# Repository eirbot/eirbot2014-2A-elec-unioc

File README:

Avant commencer, je ecris cette README pour aider les personnes que veulent participer du projet electronique pour 2014 (et pour souvenir que je [Felipe] suis bresilien, donc il aura des erreurs de français [ne hesite pas en corrigir])
Pour utilizer correctement ce repositoire, les pas suivants doivent etre suivis:
-2. Inscrivez-vous sur https://github.com/ (c'est facile, il demande seulement un nom d'utilisateur, mot de passe et e-mail)
-1. Comuniquez au responsable (Loic, je pense) pour vous inscriver sur elec_2014
0. Lisez cette README.
1. Telechargez le derniere version de KiCAD
2. Telechargez le GitHub (le method le plus facile est cliquer sur le bouton "Clone in Desktop")
3. Avec GitHub instalé, faisez le login sur le logiciel et demandez pour que le repositoire être syncronisé.
4. Les archives vont être dans <~/Mes Documents/GitHub>. Vous pouvez leur changer, mais aprés vous devez faire la syncronisation avec GitHub

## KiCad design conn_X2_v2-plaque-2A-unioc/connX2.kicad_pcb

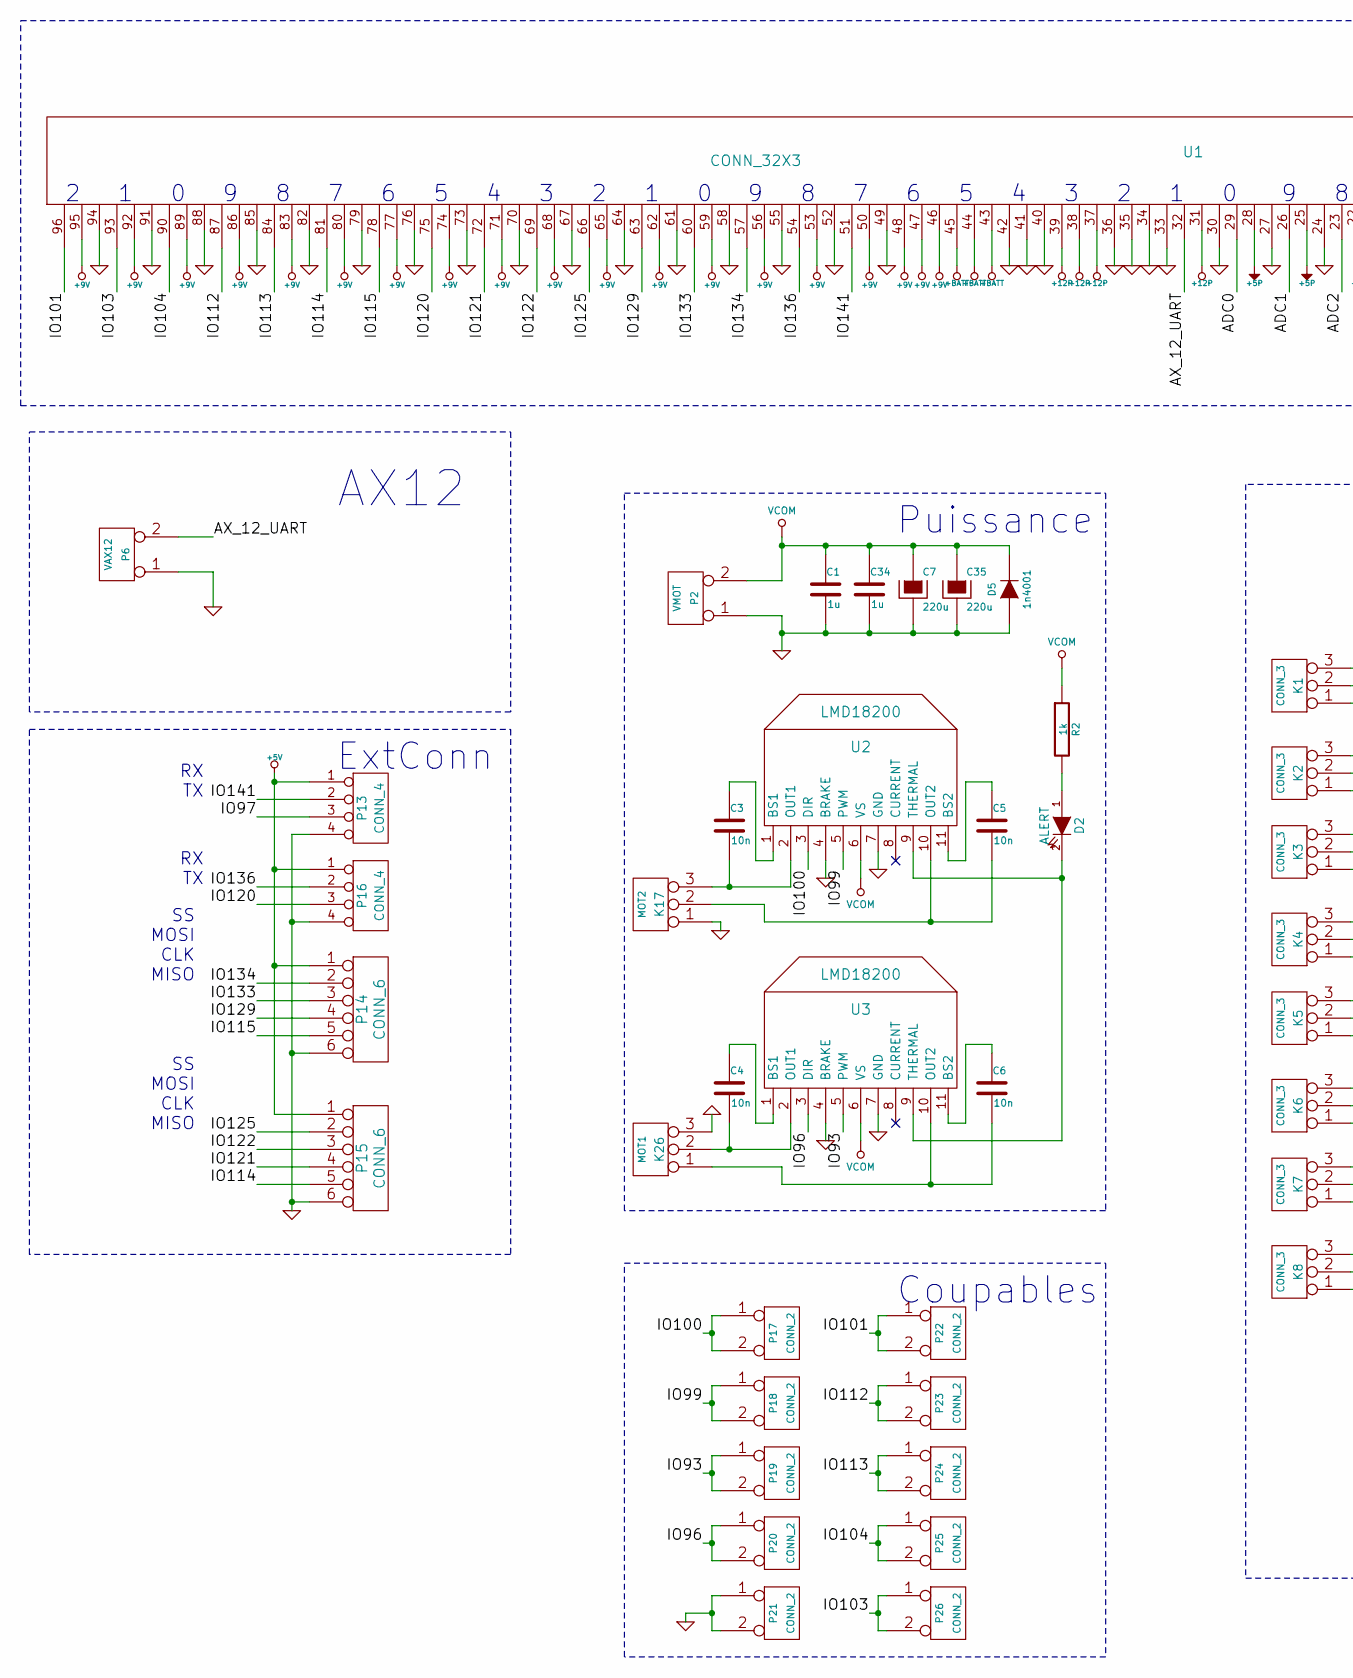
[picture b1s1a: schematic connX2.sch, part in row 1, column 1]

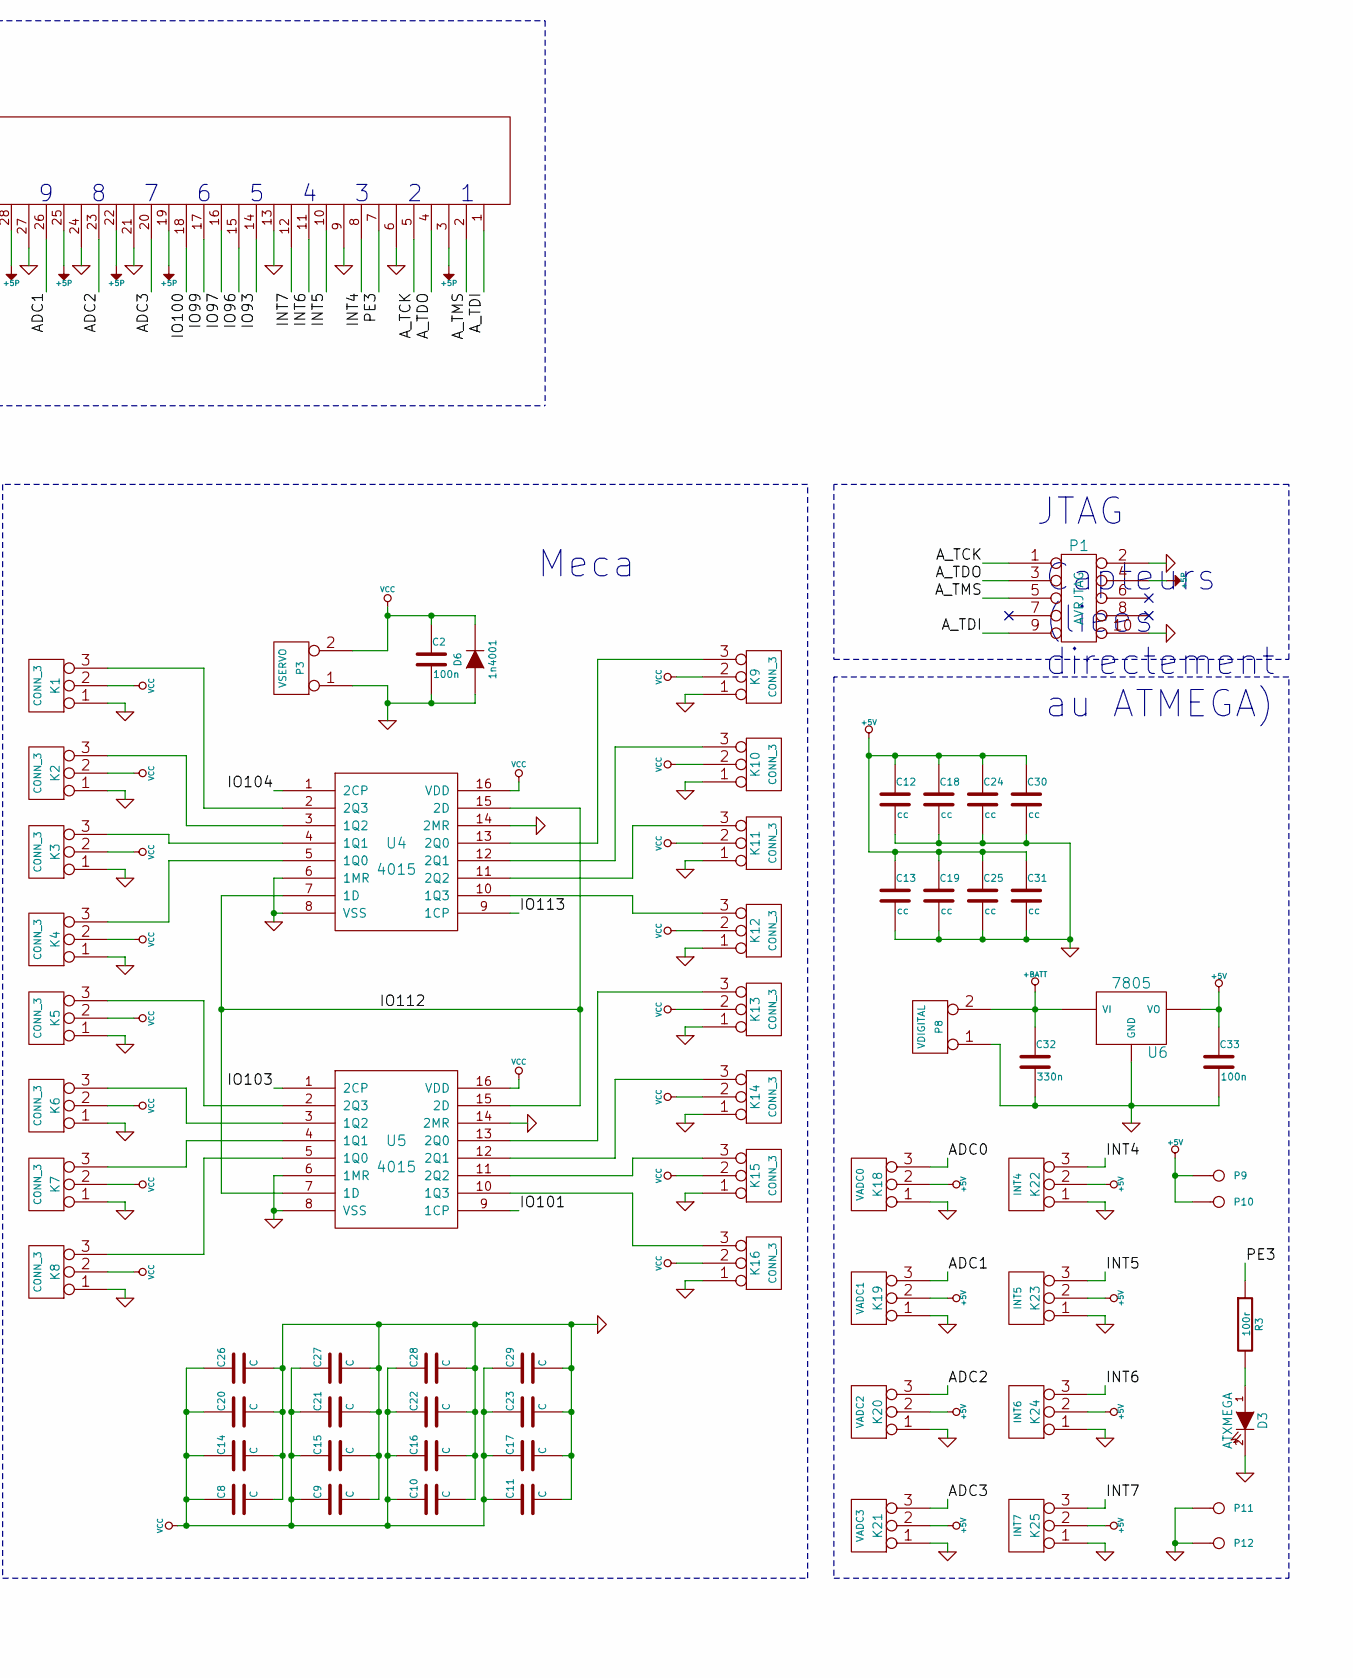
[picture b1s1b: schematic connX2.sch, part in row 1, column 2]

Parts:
C1, C34: 1u
C2, C33: 100n
C3, C4, C5, C6: 10n
C7, C35: 220u
C8, C9, C10, C11, C14, C15, C16, C17, C20, C21, C22, C23, C26, C27, C28, C29: C
C12, C13, C18, C19, C24, C25, C30, C31: cc
C32: 330n
D2: ALERT
D3: ATXMEGA
D5, D6: 1n4001
K1, K2, K3, K4, K5, K6, K7, K8, K9, K10, K11, K12, K13, K14, K15, K16: CONN_3
K17: MOT2
K18: VADC0
K19: VADC1
K20: VADC2
K21: VADC3
K22: INT4
K23: INT5
K24: INT6
K25: INT7
K26: MOT1
P1: AVRJTAG
P2: VMOT
P3: VSERVO
P6: VAX12
P8: VDIGITAL
P9, P10, P11, P12: CONN_1
P13, P16: CONN_4
P14, P15: CONN_6
P17, P18, P19, P20, P21, P22, P23, P24, P25, P26: CONN_2
R2: 1k
R3: 100r
U1: CONN_32X3
U2, U3: LMD18200
U4, U5: 4015
U6: 7805

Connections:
+5P: P1.4, U1.3, U1.19, U1.22, U1.25, U1.28
+5V: C12.1, C13.1, C18.1, C19.1, C24.1, C25.1, C30.1, C31.1, C33.1, K18.2 (PM), K19.2 (PM), K20.2 (PM), K21.2 (PM), K22.2 (PM), K23.2 (PM), K24.2 (PM), K25.2 (PM), P9.1, P10.1, P13.1, P14.1, P15.1, P16.1, U6.VO
+9V: U1.46, U1.47, U1.48, U1.50, U1.53, U1.56, U1.59, U1.62, U1.65, U1.68, U1.71, U1.74, U1.77, U1.80, U1.83, U1.86, U1.89, U1.92, U1.95
+12P: U1.31, U1.37, U1.38, U1.39
+BATT: C32.1, P8.2 (PM), U1.43, U1.44, U1.45, U6.VI
/ADC0: K18.3, U1.29
/ADC1: K19.3, U1.26
/ADC2: K20.3, U1.23
/ADC3: K21.3, U1.20
/AX_12_UART: P6.2 (PM), U1.32
/A_TCK: P1.1, U1.5
/A_TDI: P1.9, U1.1
/A_TDO: P1.3, U1.4
/A_TMS: P1.5, U1.2
/INT4: K22.3, U1.8
/INT5: K23.3, U1.10
/INT6: K24.3, U1.11
/INT7: K25.3, U1.12
/IO93: P19.1, P19.2 (PM), U1.14, U3.5 (PWM)
/IO96: P20.1, P20.2 (PM), U1.15, U3.3 (DIR)
/IO97: P13.3, U1.16
/IO99: P18.1, P18.2 (PM), U1.17, U2.5 (PWM)
/IO100: P17.1, P17.2 (PM), U1.18, U2.3 (DIR)
/IO101: P22.1, P22.2 (PM), U1.96, U5.9 (1CP)
/IO103: P26.1, P26.2 (PM), U1.93, U5.1 (2CP)
/IO104: P25.1, P25.2 (PM), U1.90, U4.1 (2CP)
/IO112: P23.1, P23.2 (PM), U1.87, U4.7 (1D), U4.15 (2D), U5.7 (1D), U5.15 (2D)
/IO113: P24.1, P24.2 (PM), U1.84, U4.9 (1CP)
/IO114: P15.5, U1.81
/IO115: P14.5, U1.78
/IO120: P16.3, U1.75
/IO121: P15.4, U1.72
/IO122: P15.3, U1.69
/IO125: P15.2, U1.66
/IO129: P14.4, U1.63
/IO133: P14.3, U1.60
/IO134: P14.2, U1.57
/IO136: P16.2, U1.54
/IO141: P13.2, U1.51
/PE3: R3.1, U1.7
GND: C1.2, C2.2, C7.2, C8.2, C9.2, C10.2, C11.2, C12.2, C13.2, C14.2, C15.2, C16.2, C17.2, C18.2, C19.2, C20.2, C21.2, C22.2, C23.2, C24.2, C25.2, C26.2, C27.2, C28.2, C29.2, C30.2, C31.2, C32.2, C33.2, C34.2, C35.2, D3.2 (K), D5.1 (A), D6.1 (A), K1.1, K2.1, K3.1, K4.1, K5.1, K6.1, K7.1, K8.1, K9.1, K10.1, K11.1, K12.1, K13.1, K14.1, K15.1, K16.1, K17.1, K18.1, K19.1, K20.1, K21.1, K22.1, K23.1, K24.1, K25.1, K26.3, P1.2, P1.10, P2.1, P3.1, P6.1, P8.1, P11.1, P12.1, P13.4, P14.6, P15.6, P16.4, P21.1, P21.2 (PM), U1.6, U1.9, U1.13, U1.21, U1.24, U1.27, U1.30, U1.33, U1.34, U1.35, U1.36, U1.40, U1.41, U1.42, U1.49, U1.52, U1.55, U1.58, U1.61, U1.64, U1.67, U1.70, U1.73, U1.76, U1.79, U1.82, U1.85, U1.88, U1.91, U1.94, U2.4 (BRAKE), U2.7 (GND), U3.4 (BRAKE), U3.7 (GND), U4.6 (1MR), U4.8 (VSS), U4.14 (2MR), U5.6 (1MR), U5.8 (VSS), U5.14 (2MR), U6.GND
unnamed: D2.2 (K), U2.9 (THERMAL), U3.9 (THERMAL)
unnamed: D2.1 (A), R2.2
unnamed: C6.1, U3.11 (BS2)
unnamed: C5.1, U2.11 (BS2)
unnamed: C3.1, U2.1 (BS1)
unnamed: C3.2, K17.3, U2.2 (OUT1)
unnamed: D3.1 (A), R3.2
unnamed: C4.1, U3.1 (BS1)
unnamed: C4.2, K26.2 (PM), U3.2 (OUT1)
unnamed: C5.2, K17.2 (PM), U2.10 (OUT2)
unnamed: C6.2, K26.1, U3.10 (OUT2)
unnamed: K12.3, U4.10 (1Q3)
unnamed: K4.3, U4.5 (1Q0)
unnamed: K3.3, U4.4 (1Q1)
unnamed: K2.3, U4.3 (1Q2)
unnamed: K1.3, U4.2 (2Q3)
unnamed: K11.3, U4.11 (2Q2)
unnamed: K10.3, U4.12 (2Q1)
unnamed: K9.3, U4.13 (2Q0)
unnamed: K7.3, U5.4 (1Q1)
unnamed: K8.3, U5.5 (1Q0)
unnamed: K6.3, U5.3 (1Q2)
unnamed: K5.3, U5.2 (2Q3)
unnamed: K16.3, U5.10 (1Q3)
unnamed: K15.3, U5.11 (2Q2)
unnamed: K14.3, U5.12 (2Q1)
unnamed: K13.3, U5.13 (2Q0)
VCC: C2.1, C8.1, C9.1, C10.1, C11.1, C14.1, C15.1, C16.1, C17.1, C20.1, C21.1, C22.1, C23.1, C26.1, C27.1, C28.1, C29.1, D6.2 (K), K1.2 (PM), K2.2 (PM), K3.2 (PM), K4.2 (PM), K5.2 (PM), K6.2 (PM), K7.2 (PM), K8.2 (PM), K9.2 (PM), K10.2 (PM), K11.2 (PM), K12.2 (PM), K13.2 (PM), K14.2 (PM), K15.2 (PM), K16.2 (PM), P3.2 (PM), U4.16 (VDD), U5.16 (VDD)
VCOM: C1.1, C7.1, C34.1, C35.1, D5.2 (K), P2.2 (PM), R2.1, U2.6 (VS), U3.6 (VS)

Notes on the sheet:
9 8 7 6 5 4 3 2 1
9 8 7 6 5 4 3 2 1 0
2 1 0
Puissance
Capteurs (liees directement au ATMEGA)
JTAG
Meca
SS MOSI CLK MISO
ExtConn
RX TX
Coupables
AX12

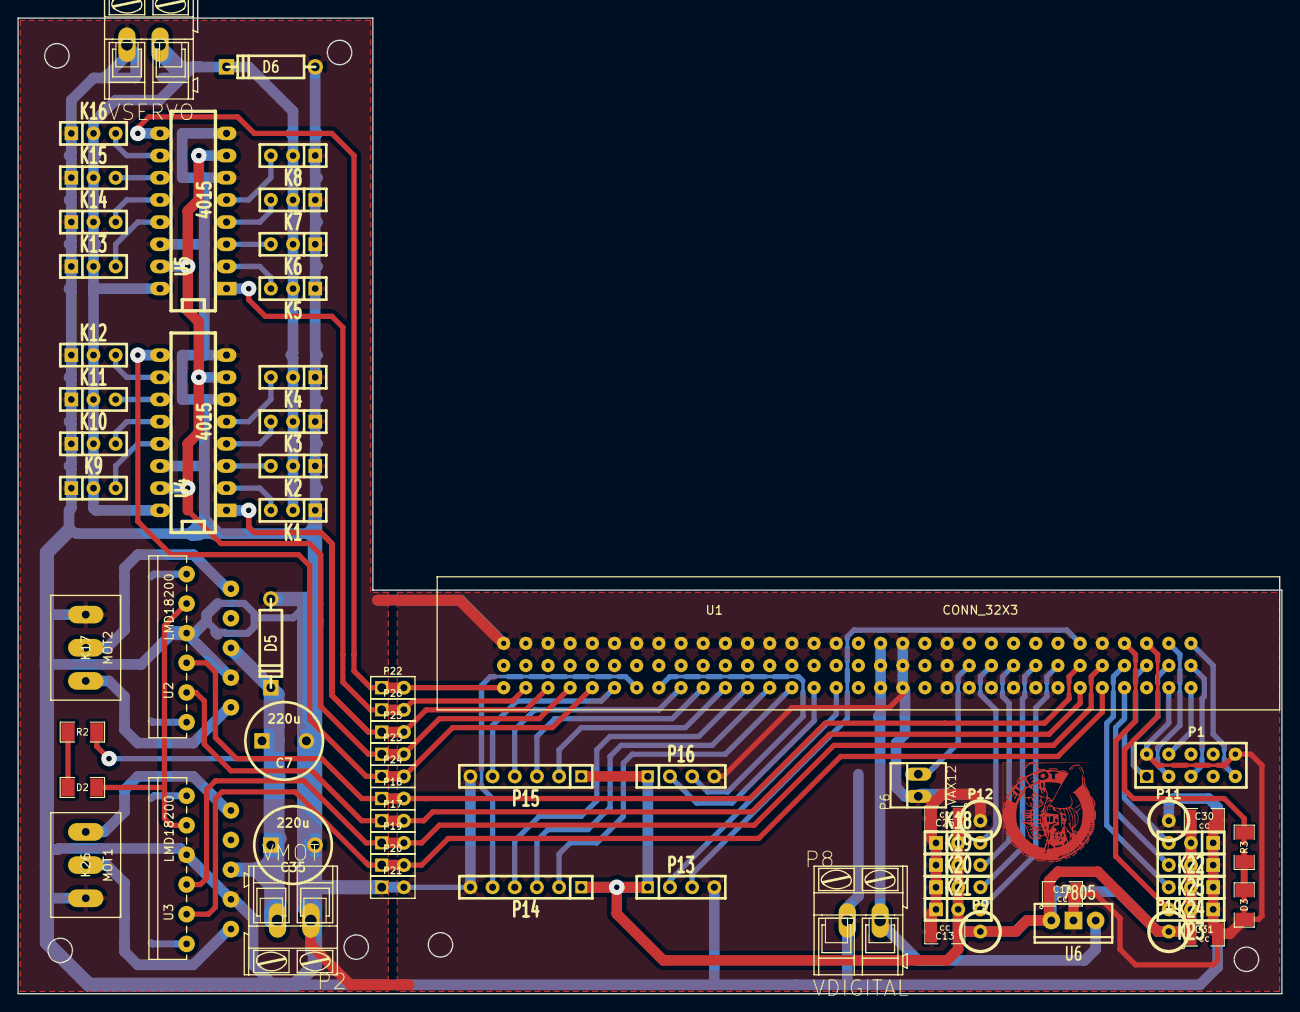
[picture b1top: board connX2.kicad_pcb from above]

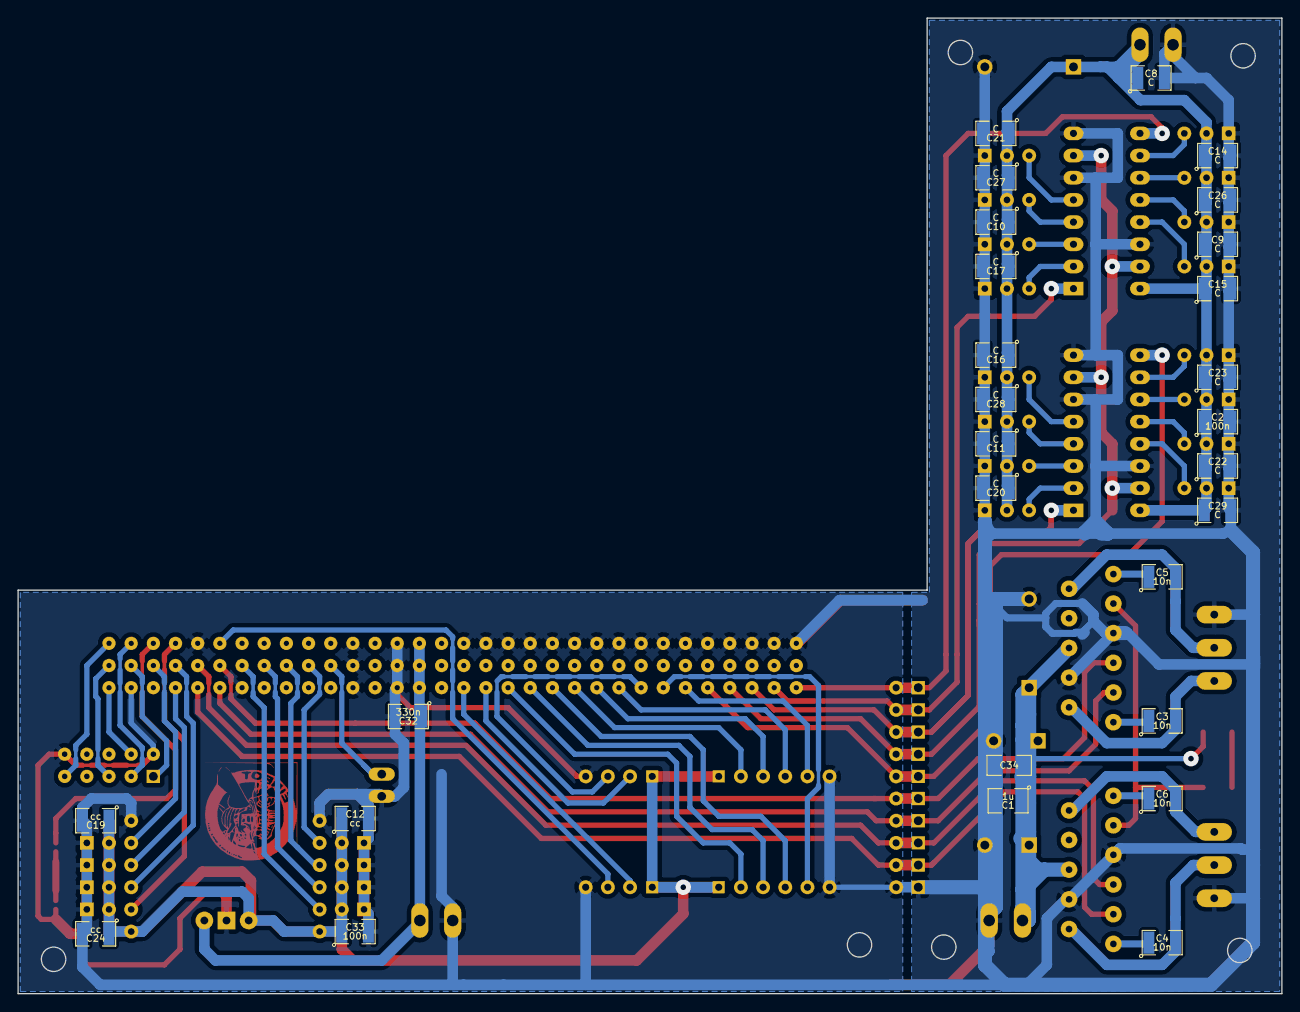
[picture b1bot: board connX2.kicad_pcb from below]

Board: 2 copper layers, 144.8 x 111.8 mm, 96 parts (28 on the bottom side), 70 nets.

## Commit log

2013-07-06 Début de dépôt
2013-07-11 Début du projet, création du premier schématique.
2013-07-12 Ajout du FPGA de robotter.
2013-09-24 Ajour du document de conception
2013-09-25 Nouvelle architecture (test)
2013-09-25 Readme modifié
2013-09-26 Creation de lib + LMD18200
2013-09-28 LOGO EIRBORT
    celle-ci a eté dificile a faire
2013-10-27 Code VHDL codename exmachine
2013-11-08 Projet (presque) complet
2014-01-16 projet complet (?)
2014-02-01 UNIOC complete
2014-05-08 Carte adaptateur X2
2014-12-04 Atualization Codeurs
